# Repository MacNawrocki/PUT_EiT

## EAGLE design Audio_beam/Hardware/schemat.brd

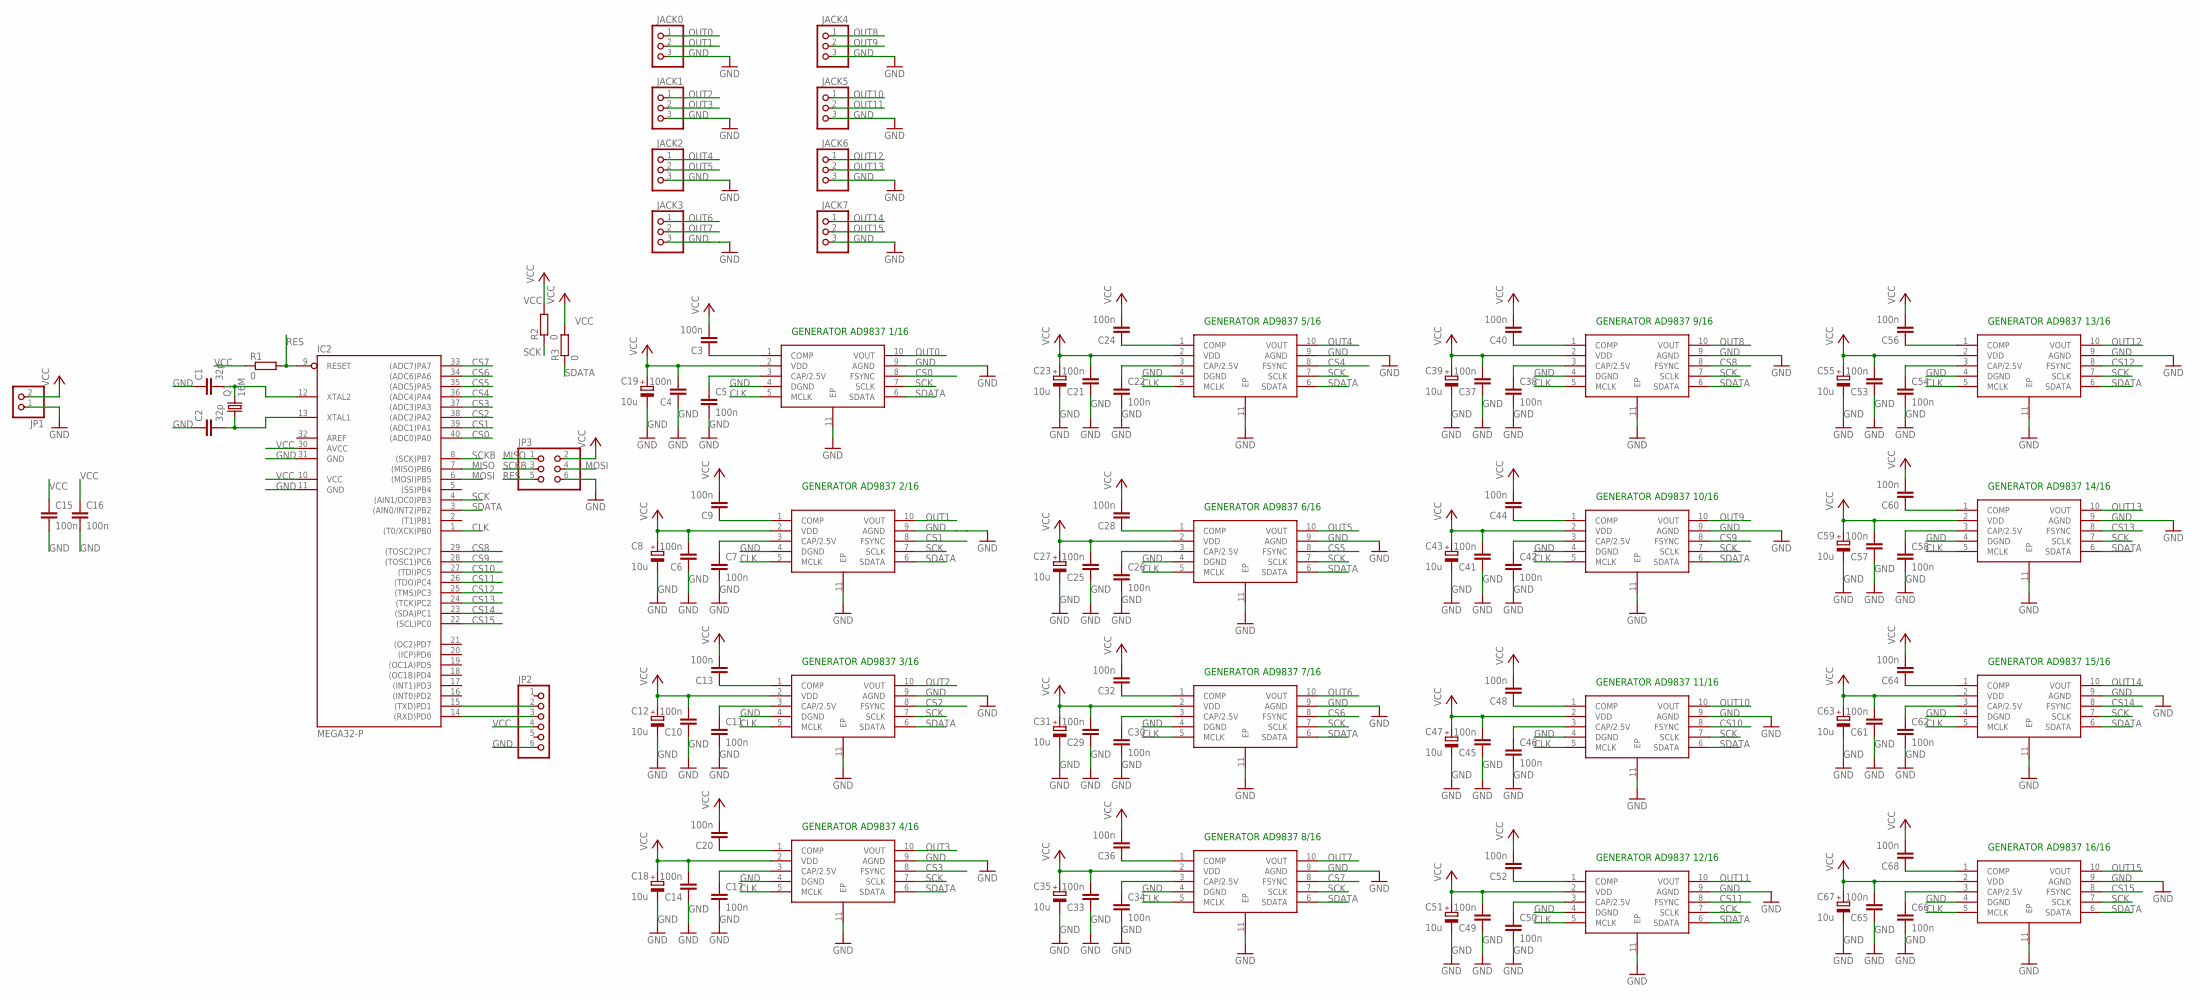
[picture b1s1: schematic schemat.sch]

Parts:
C1, C2: 32p; C1206
C3, C4, C5, C6, C7, C9, C10, C11, C13, C14, C15, C16, C17, C20, C21, C22, C24, C25, C26, C28, C29, C30, C32, C33, C34, C36, C37, C38, C40, C41, C42, C44, C45, C46, C48, C49, C50, C52, C53, C54, C56, C57, C58, C60, C61, C62, C64, C65, C66, C68: 100n; C1206
C8, C12, C18, C19, C23, C27, C31, C35, C39, C43, C47, C51, C55, C59, C63, C67: 10u; SMC_B
GEN1, GEN2, GEN3, GEN4, GEN5, GEN6, GEN7, GEN8, GEN9, GEN10, GEN11, GEN12, GEN13, GEN14, GEN15, GEN16: AD9837; SON50P300X300X80-11N
IC2: MEGA32-P; DIL40
JACK0, JACK1, JACK2, JACK3, JACK4, JACK5, JACK6, JACK7: PINHD-1X3; 1X03
JP1: PINHD-1X2; 1X02
JP2: PINHD-1X6; 1X06
JP3: PINHD-2X3; 2X03
Q1: 16M; HC49/S
R1: 0; R1206
R2, R3: 0; M1206

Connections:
CLK: GEN1.5 (MCLK), GEN2.5 (MCLK), GEN3.5 (MCLK), GEN4.5 (MCLK), GEN5.5 (MCLK), GEN6.5 (MCLK), GEN7.5 (MCLK), GEN8.5 (MCLK), GEN9.5 (MCLK), GEN10.5 (MCLK), GEN11.5 (MCLK), GEN12.5 (MCLK), GEN13.5 (MCLK), GEN14.5 (MCLK), GEN15.5 (MCLK), GEN16.5 (MCLK), IC2.1 ((T0/XCK)PB0)
CS0: GEN1.8 (FSYNC), IC2.40 ((ADC0)PA0)
CS1: GEN2.8 (FSYNC), IC2.39 ((ADC1)PA1)
CS2: GEN3.8 (FSYNC), IC2.38 ((ADC2)PA2)
CS3: GEN4.8 (FSYNC), IC2.37 ((ADC3)PA3)
CS4: GEN5.8 (FSYNC), IC2.36 ((ADC4)PA4)
CS5: GEN6.8 (FSYNC), IC2.35 ((ADC5)PA5)
CS6: GEN7.8 (FSYNC), IC2.34 ((ADC6)PA6)
CS7: GEN8.8 (FSYNC), IC2.33 ((ADC7)PA7)
CS8: GEN9.8 (FSYNC), IC2.29 ((TOSC2)PC7)
CS9: GEN10.8 (FSYNC), IC2.28 ((TOSC1)PC6)
CS10: GEN11.8 (FSYNC), IC2.27 ((TDI)PC5)
CS11: GEN12.8 (FSYNC), IC2.26 ((TDO)PC4)
CS12: GEN13.8 (FSYNC), IC2.25 ((TMS)PC3)
CS13: GEN14.8 (FSYNC), IC2.24 ((TCK)PC2)
CS14: GEN15.8 (FSYNC), IC2.23 ((SDA)PC1)
CS15: GEN16.8 (FSYNC), IC2.22 ((SCL)PC0)
GND: C1.1, C2.1, C4.1, C5.2, C6.1, C7.2, C8.-, C10.1, C11.2, C12.-, C14.1, C15.2, C16.2, C17.2, C18.-, C19.-, C21.1, C22.2, C23.-, C25.1, C26.2, C27.-, C29.1, C30.2, C31.-, C33.1, C34.2, C35.-, C37.1, C38.2, C39.-, C41.1, C42.2, C43.-, C45.1, C46.2, C47.-, C49.1, C50.2, C51.-, C53.1, C54.2, C55.-, C57.1, C58.2, C59.-, C61.1, C62.2, C63.-, C65.1, C66.2, C67.-, GEN1.4 (DGND), GEN1.9 (AGND), GEN1.11 (EP), GEN2.4 (DGND), GEN2.9 (AGND), GEN2.11 (EP), GEN3.4 (DGND), GEN3.9 (AGND), GEN3.11 (EP), GEN4.4 (DGND), GEN4.9 (AGND), GEN4.11 (EP), GEN5.4 (DGND), GEN5.9 (AGND), GEN5.11 (EP), GEN6.4 (DGND), GEN6.9 (AGND), GEN6.11 (EP), GEN7.4 (DGND), GEN7.9 (AGND), GEN7.11 (EP), GEN8.4 (DGND), GEN8.9 (AGND), GEN8.11 (EP), GEN9.4 (DGND), GEN9.9 (AGND), GEN9.11 (EP), GEN10.4 (DGND), GEN10.9 (AGND), GEN10.11 (EP), GEN11.4 (DGND), GEN11.9 (AGND), GEN11.11 (EP), GEN12.4 (DGND), GEN12.9 (AGND), GEN12.11 (EP), GEN13.4 (DGND), GEN13.9 (AGND), GEN13.11 (EP), GEN14.4 (DGND), GEN14.9 (AGND), GEN14.11 (EP), GEN15.4 (DGND), GEN15.9 (AGND), GEN15.11 (EP), GEN16.4 (DGND), GEN16.9 (AGND), GEN16.11 (EP), IC2.11 (GND), IC2.31 (GND), JACK0.3, JACK1.3, JACK2.3, JACK3.3, JACK4.3, JACK5.3, JACK6.3, JACK7.3, JP1.1, JP2.6, JP3.6
MISO: IC2.7 ((MISO)PB6), JP3.1
MOSI: IC2.6 ((MOSI)PB5), JP3.4
unnamed: C7.1, GEN2.3 (CAP/2.5V)
unnamed: C9.1, GEN2.1 (COMP)
unnamed: C1.2, IC2.12 (XTAL2), Q1.2
unnamed: C2.2, IC2.13 (XTAL1), Q1.1
unnamed: C5.1, GEN1.3 (CAP/2.5V)
unnamed: C11.1, GEN3.3 (CAP/2.5V)
unnamed: C13.1, GEN3.1 (COMP)
unnamed: C17.1, GEN4.3 (CAP/2.5V)
unnamed: C20.1, GEN4.1 (COMP)
unnamed: C22.1, GEN5.3 (CAP/2.5V)
unnamed: C24.1, GEN5.1 (COMP)
unnamed: C3.1, GEN1.1 (COMP)
unnamed: C26.1, GEN6.3 (CAP/2.5V)
unnamed: C28.1, GEN6.1 (COMP)
unnamed: C30.1, GEN7.3 (CAP/2.5V)
unnamed: C32.1, GEN7.1 (COMP)
unnamed: C34.1, GEN8.3 (CAP/2.5V)
unnamed: C36.1, GEN8.1 (COMP)
unnamed: C38.1, GEN9.3 (CAP/2.5V)
unnamed: C40.1, GEN9.1 (COMP)
unnamed: C42.1, GEN10.3 (CAP/2.5V)
unnamed: C44.1, GEN10.1 (COMP)
unnamed: C46.1, GEN11.3 (CAP/2.5V)
unnamed: C48.1, GEN11.1 (COMP)
unnamed: C50.1, GEN12.3 (CAP/2.5V)
unnamed: C52.1, GEN12.1 (COMP)
unnamed: C54.1, GEN13.3 (CAP/2.5V)
unnamed: C56.1, GEN13.1 (COMP)
unnamed: C58.1, GEN14.3 (CAP/2.5V)
unnamed: C60.1, GEN14.1 (COMP)
unnamed: C62.1, GEN15.3 (CAP/2.5V)
unnamed: C64.1, GEN15.1 (COMP)
unnamed: C66.1, GEN16.3 (CAP/2.5V)
unnamed: C68.1, GEN16.1 (COMP)
unnamed: IC2.15 ((TXD)PD1), JP2.2
unnamed: IC2.14 ((RXD)PD0), JP2.3
OUT0: GEN1.10 (VOUT), JACK0.1
OUT1: GEN2.10 (VOUT), JACK0.2
OUT2: GEN3.10 (VOUT), JACK1.1
OUT3: GEN4.10 (VOUT), JACK1.2
OUT4: GEN5.10 (VOUT), JACK2.1
OUT5: GEN6.10 (VOUT), JACK2.2
OUT6: GEN7.10 (VOUT), JACK3.1
OUT7: GEN8.10 (VOUT), JACK3.2
OUT8: GEN9.10 (VOUT), JACK4.1
OUT9: GEN10.10 (VOUT), JACK4.2
OUT10: GEN11.10 (VOUT), JACK5.1
OUT11: GEN12.10 (VOUT), JACK5.2
OUT12: GEN13.10 (VOUT), JACK6.1
OUT13: GEN14.10 (VOUT), JACK6.2
OUT14: GEN15.10 (VOUT), JACK7.1
OUT15: GEN16.10 (VOUT), JACK7.2
RES: IC2.9 (RESET), JP3.5, R1.2
SCK: GEN1.7 (SCLK), GEN2.7 (SCLK), GEN3.7 (SCLK), GEN4.7 (SCLK), GEN5.7 (SCLK), GEN6.7 (SCLK), GEN7.7 (SCLK), GEN8.7 (SCLK), GEN9.7 (SCLK), GEN10.7 (SCLK), GEN11.7 (SCLK), GEN12.7 (SCLK), GEN13.7 (SCLK), GEN14.7 (SCLK), GEN15.7 (SCLK), GEN16.7 (SCLK), IC2.4 ((AIN1/OC0)PB3), R2.1
SCKB: IC2.8 ((SCK)PB7), JP3.3
SDATA: GEN1.6 (SDATA), GEN2.6 (SDATA), GEN3.6 (SDATA), GEN4.6 (SDATA), GEN5.6 (SDATA), GEN6.6 (SDATA), GEN7.6 (SDATA), GEN8.6 (SDATA), GEN9.6 (SDATA), GEN10.6 (SDATA), GEN11.6 (SDATA), GEN12.6 (SDATA), GEN13.6 (SDATA), GEN14.6 (SDATA), GEN15.6 (SDATA), GEN16.6 (SDATA), IC2.3 ((AIN0/INT2)PB2), R3.1
VCC: C3.2, C4.2, C6.2, C8.+, C9.2, C10.2, C12.+, C13.2, C14.2, C15.1, C16.1, C18.+, C19.+, C20.2, C21.2, C23.+, C24.2, C25.2, C27.+, C28.2, C29.2, C31.+, C32.2, C33.2, C35.+, C36.2, C37.2, C39.+, C40.2, C41.2, C43.+, C44.2, C45.2, C47.+, C48.2, C49.2, C51.+, C52.2, C53.2, C55.+, C56.2, C57.2, C59.+, C60.2, C61.2, C63.+, C64.2, C65.2, C67.+, C68.2, GEN1.2 (VDD), GEN2.2 (VDD), GEN3.2 (VDD), GEN4.2 (VDD), GEN5.2 (VDD), GEN6.2 (VDD), GEN7.2 (VDD), GEN8.2 (VDD), GEN9.2 (VDD), GEN10.2 (VDD), GEN11.2 (VDD), GEN12.2 (VDD), GEN13.2 (VDD), GEN14.2 (VDD), GEN15.2 (VDD), GEN16.2 (VDD), IC2.10 (VCC), IC2.30 (AVCC), JP1.2, JP2.4, JP3.2, R1.1, R2.2, R3.2

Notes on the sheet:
GENERATOR AD9837 1/16
GENERATOR AD9837 2/16
GENERATOR AD9837 3/16
GENERATOR AD9837 4/16
GENERATOR AD9837 5/16
GENERATOR AD9837 6/16
GENERATOR AD9837 7/16
GENERATOR AD9837 8/16
GENERATOR AD9837 9/16
GENERATOR AD9837 10/16
GENERATOR AD9837 11/16
GENERATOR AD9837 12/16
GENERATOR AD9837 13/16
GENERATOR AD9837 14/16
GENERATOR AD9837 15/16
GENERATOR AD9837 16/16

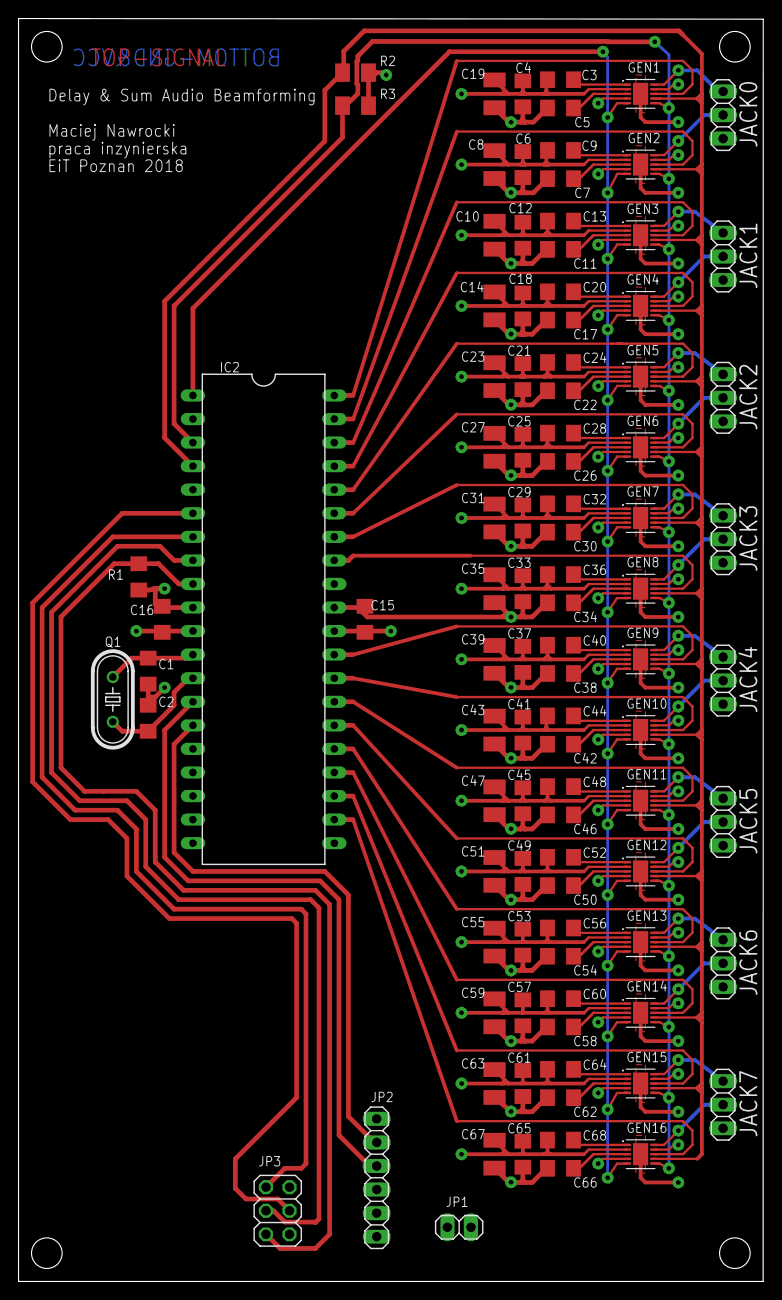
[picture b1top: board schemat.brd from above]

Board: 2 copper layers, 80.3 x 136.1 mm, 100 parts (0 on the bottom side), 77 nets.

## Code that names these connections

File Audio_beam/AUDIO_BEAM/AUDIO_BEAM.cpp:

//#ifndef F_CPU
//#define F_CPU 16000000UL
//#endif

#include <avr/io.h>
#include <math.h>
//#include <util/delay.h> 

//Chip Select 0
#define CSEL0 PA0
#define CSEL0_DDR	DDRA
#define CSEL0_PORT PORTA
//Chip Select 1
#define CSEL1 PA1
#define CSEL1_DDR	DDRA
#define CSEL1_PORT PORTA
//Chip Select 2
#define CSEL2 PA2
#define CSEL2_DDR	DDRA
#define CSEL2_PORT PORTA
//Chip Select 3
#define CSEL3 PA3
#define CSEL3_DDR	DDRA
#define CSEL3_PORT PORTA
//Chip Select 4
#define CSEL4 PA4
#define CSEL4_DDR	DDRA
#define CSEL4_PORT PORTA
//Chip Select 5
#define CSEL5 PA5
#define CSEL5_DDR	DDRA
#define CSEL5_PORT PORTA
//Chip Select 6
#define CSEL6 PA6
#define CSEL6_DDR	DDRA
#define CSEL6_PORT PORTA
//Chip Select 7
#define CSEL7 PA7
#define CSEL7_DDR	DDRA
#define CSEL7_PORT PORTA
//Chip Select 8
#define CSEL8 PC7
#define CSEL8_DDR	DDRC
#define CSEL8_PORT PORTC
//Chip Select 9
#define CSEL9 PC6
#define CSEL9_DDR	DDRC
#define CSEL9_PORT PORTC
//Chip Select 10
#define CSEL10 PC5
#define CSEL10_DDR	DDRC
#define CSEL10_PORT PORTC
//Chip Select 11
#define CSEL11 PC4
#define CSEL11_DDR	DDRC
#define CSEL11_PORT PORTC
//Chip Select 12
#define CSEL12 PC3
#define CSEL12_DDR	DDRC
#define CSEL12_PORT PORTC
//Chip Select 13
#define CSEL13 PC2
#define CSEL13_DDR	DDRC
#define CSEL13_PORT PORTC
//Chip Select 14
#define CSEL14 PC1
#define CSEL14_DDR	DDRC
#define CSEL14_PORT PORTC
//Chip Select 15
#define CSEL15 PC0
#define CSEL15_DDR	DDRC
#define CSEL15_PORT PORTC
//SCK do Software SPI
#define SCK PB3
#define SCK_DDR	DDRB
#define SCK_PORT PORTB
//SDATA do Software SPI
#define SDATA PB2
#define SDATA_DDR DDRB
#define SDATA_PORT PORTB
//CLK jako Fmclk czyli sygnał zegarowy referencyjny
#define CLK PB0
#define CLK_DDR DDRB
#define CLK_PORT PORTB

//Funkcje Software SPI 
//#define SET_INPUT(pin)			((pin ## _DDR) &= !_BV(pin) )
//#define SET_OUTPUT(ddr, pin)		(ddr |= (1<<pin))
#define SET_HIGH(pin)				((pin ## _PORT) |= _BV(pin))
#define SET_LOW(pin)				((pin ## _PORT) &= !_BV(pin))

#define TABSIZE 16
uint32_t phaseArray[TABSIZE];
//Czestotliwość fmclk - do przeliczania czestotliwosci oraz podawana na linii CLK
const float freqRef = 158000; 
uint16_t CalcPhase (uint32_t phase);
uint32_t CalcFreq(uint32_t freq);
void SPIconfig();
void SPIrefresh();
inline void SPIsend(uint16_t data); 
inline void SetAllCS_Low();
inline void SetAllCS_High();
void CalcPhaseVal(uint32_t freq, uint32_t dist);

//funkcja oblicza opóźnienia fazowe dla każdego generatora
void CalcPhaseVal(uint32_t freq, uint32_t dist)
{
	uint32_t spacing = 0.0725;//m    
    uint32_t speedSound = 343.0;// m/s
    uint32_t distxTab[TABSIZE];
    uint32_t maxdistx = spacing*7;
    for (int i = 0; i<TABSIZE; i++){
        if (i<7)distxTab[i]=(maxdistx-i*spacing)+spacing/2;
        if (i == 7)distxTab[i]=spacing/2;
        if (i == 8)distxTab[i]=spacing/2;
        if (i>8) distxTab[i]=spacing/2 + (i-8)*spacing;
    }
    uint32_t distRealTab[TABSIZE];
    for (int i = 0; i<TABSIZE; i++){
        distRealTab[i]=sqrt(pow(distxTab[i],2)+pow(dist,2));
    }
    uint32_t delayTab[TABSIZE];
    uint32_t delayzero=distRealTab[7]*speedSound;
    for (int i = 0; i<TABSIZE; i++){
        delayTab[i]=(distRealTab[i]*speedSound)-delayzero;
        phaseArray[i] = (1 - ((delayTab[i]/(1/freq))-floor((delayTab[i]/(1/freq)))))*2*3.14159265358979;
    }
}

//funkcja przelicza częstotliwość w Hz na dane do generatora
uint32_t CalcFreq(uint32_t freq)
{
	//f = fMCLK/2^28 × FREQREG
	float freqRes = 0x10000000;
	float stepSize;
	stepSize = freqRes/freqRef;
	
	uint32_t freqWord;
	freqWord = stepSize*freq;
	return freqWord;
}

//funkcja przelicza fazę na dane do generatora, faza podana w radianach
uint16_t CalcPhase (uint32_t phase)
{
	//2π/4096 × PHASEREG
	float phaseRes; 
	phaseRes = 4096/(2*3.14159265358979);
	uint16_t phaseWord;
	phaseWord = phase*phaseRes;
	return phaseWord;
}

//Konfiguracja pinów i ich rejestrów do SPI
void SPIconfig() 
{
	SCK_DDR|=1<<3; // SET_OUTPUT(SCK_DDR, SCK);
	SDATA_DDR|=1<<2; // SET_OUTPUT(SDATA_DDR,SDATA);
	//Rejestr DDR portu A zapełniony 1 - piny CSel0-7
	DDRA = 0b11111111;
	//Rejestr DDR portu C zapełniony 1 - piny CSel8-15
	DDRC = 0b11111111;
	SET_HIGH(SCK);
	SET_HIGH(SDATA);
	//Stan wysoki wszystkich FSYNC 
	PORTA = 0b11111111;
	PORTC = 0b11111111;
}

//Ustanowienie domyślnych wartości na portach SPI
void SPIrefresh()
{
	//Stan wysoki wszystkich FSYNC 
	PORTA = 0b11111111;
	PORTC = 0b11111111;
	SET_LOW(SDATA);
	SET_HIGH(SCK);
}

//Stan niski wszystkich FSYNC - dane odbierają wszystkie generatory
inline void SetAllCS_Low()
{
	PORTA = 0b00000000;
	PORTC = 0b00000000;
}

//Stan wysoki wszystkich FSYNC 
inline void SetAllCS_High()
{
	PORTA = 0b11111111;
	PORTC = 0b11111111;
}

//Funkcja software'owo realizuje komunikacje SPI - wysyła jeden wyraz
inline void SPIsend(uint16_t data) 
{
	for(uint16_t mask= 0x8000; mask; mask>>=1) 
	{
		SET_HIGH(SCK);
		if(data & mask) SET_HIGH(SDATA);
		else SET_LOW(SDATA);
		SET_LOW(SCK);
	}
}



int main(void)
{ 
	uint32_t freq = 5000; // częstotliwość generowanych sygnałów w Hz
	uint32_t dist = 2; // odległość punktu wzmocnienia sygnału od środka wektora głośników w m
	
	//kalkulowanie częstotliwości
	uint32_t freqWord = CalcFreq(freq);
	//wielkosc przesylanych danych do rejestru częstotliwości to 2 x 14 bit
	uint16_t freqWordMSB;
	uint16_t freqWordLSB;
	freqWordMSB = (int)((freqWord & 0xFFFC000)>>14);
	freqWordLSB = (int)(freqWord & 0x3FFF);
	//bity D15 i D14 - 01 wybierają rejestr FREQ0
	//freqWordLSB |= 0x4000;
	//freqWordMSB |= 0x4000; 
	freqWordLSB |= 0x4FFF;
	freqWordMSB |= 0x4FFF;
	
	//kalkulowanie fazy
	//wielkość przesyłanych danych do rejestru fazy to 12 bit 
	CalcPhaseVal(freq, dist);
	uint16_t phaseWordArray[TABSIZE];
	for (int i = 0; i<TABSIZE; i++){
        phaseWordArray[i]=CalcPhase(phaseArray[i]);
		//bity D15, D14, D13- 110 wybierają rejestr PHASE0
		phaseWordArray[i]|= 0xC000;
    }
	
	uint16_t initWord = 0x2100;	// bity D13 i D8 - zapis danych i RESET=1
	// RESET=0, bity D11 i  D10 = 00 - rejsestry FREQ0 i PHASE0
	uint16_t resetWordSin = 0x2000; // wyjście to sin
	uint16_t resetWordSqr = 0x2020; // wyjście to prostokąt
	uint16_t resetWordTri = 0x2002; // wyjście to trójkąt
	
	SPIconfig();
	
	//Podanie do wszystkich generatorów informacji o częstotliwości i RESET = 1
	//SetAllCS_Low();
	SET_LOW(CSEL0);	
	SPIsend(initWord); 
	SET_HIGH(CSEL0);
	//SetAllCS_High();
	SPIrefresh();
	SetAllCS_Low();	
	SPIsend(freqWordLSB);
	SetAllCS_High();
	SPIrefresh();
	SetAllCS_Low();	
	SPIsend(freqWordMSB);
	SetAllCS_High();
	SPIrefresh();
	
	/*
	//podanie do Generatora 0 informacji o fazie
	SET_LOW(CSEL0);
	SPIsend(phaseWordArray[0]);
	SET_HIGH(CSEL0);
	SPIrefresh();
	//podanie do Generatora 1 informacji o fazie
	SET_LOW(CSEL1);
	SPIsend(phaseWordArray[1]);
	SET_HIGH(CSEL1);
	SPIrefresh();
	//podanie do Generatora 2 informacji o fazie
	SET_LOW(CSEL2);
	SPIsend(phaseWordArray[2]);
	SET_HIGH(CSEL2);
	SPIrefresh();
	//podanie do Generatora 3 informacji o fazie
	SET_LOW(CSEL3);
	SPIsend(phaseWordArray[3]);
	SET_HIGH(CSEL3);
	SPIrefresh();
	//podanie do Generatora 4 informacji o fazie
	SET_LOW(CSEL4);
	SPIsend(phaseWordArray[4]);
	SET_HIGH(CSEL4);
	SPIrefresh();
	//podanie do Generatora 5 informacji o fazie
	SET_LOW(CSEL5);
	SPIsend(phaseWordArray[5]);
	SET_HIGH(CSEL5);
	SPIrefresh();
	//podanie do Generatora 6 informacji o fazie
	SET_LOW(CSEL6);
	SPIsend(phaseWordArray[6]);
	SET_HIGH(CSEL6);
	SPIrefresh();
	//podanie do Generatora 7 informacji o fazie
	SET_LOW(CSEL7);
	SPIsend(phaseWordArray[7]);
	SET_HIGH(CSEL7);
	SPIrefresh();
	//podanie do Generatora 8 informacji o fazie
	SET_LOW(CSEL8);
	SPIsend(phaseWordArray[8]);
	SET_HIGH(CSEL8);
	SPIrefresh();
	//podanie do Generatora 9 informacji o fazie
	SET_LOW(CSEL9);
	SPIsend(phaseWordArray[9]);
	SET_HIGH(CSEL9);
	SPIrefresh();
	//podanie do Generatora 10 informacji o fazie
	SET_LOW(CSEL10);
	SPIsend(phaseWordArray[10]);
	SET_HIGH(CSEL10);
	SPIrefresh();
	//podanie do Generatora 11 informacji o fazie
	SET_LOW(CSEL11);
	SPIsend(phaseWordArray[11]);
	SET_HIGH(CSEL11);
	SPIrefresh();
	//podanie do Generatora 12 informacji o fazie
	SET_LOW(CSEL12);
	SPIsend(phaseWordArray[12]);
	SET_HIGH(CSEL12);
	SPIrefresh();
	//podanie do Generatora 13 informacji o fazie
	SET_LOW(CSEL13);
	SPIsend(phaseWordArray[13]);
	SET_HIGH(CSEL13);
	//podanie do Generatora 14 informacji o fazie
	SET_LOW(CSEL14);
	SPIsend(phaseWordArray[14]);
	SET_HIGH(CSEL14);
	SPIrefresh();
	//podanie do Generatora 15 informacji o fazie
	SET_LOW(CSEL15);
	SPIsend(phaseWordArray[15]);
	SET_HIGH(CSEL15);	*/
	SPIrefresh();

	//Podanie do wszystkich generatorów informacji o trybie pracy i RESET = 0
	SetAllCS_Low();
	SPIsend(resetWordSin); 
	SetAllCS_High();
	
	//Po podaniu danych do generatorów uruchamiany jest generator CLK
	//CLK generowane tą metodą ma częstotliwość 158 kHz
	CLK_DDR|=1; // SET_OUTPUT(CLK_DDR, CLK);
	while(1)
    {
		SET_HIGH(CLK);
		SET_LOW(CLK);	
	}
	
}

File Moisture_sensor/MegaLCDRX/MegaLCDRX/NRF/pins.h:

#ifndef PINS_H_
#define PINS_H_

/*
Connection:
ATMega328PB	PIN	To
PB3	to	MOSI		programator/radio
PB4	to	MISO		programator/radio
PB5	to	SCK			programator/radio
PB6	to	CSN			radio
PB7	to	CE			radio
PC0	to	LCD_RST		wywietlacz
PC1	to	LCD_AO		wywietlacz
PC2	to	LCD_MOSI	wywietlacz
PC3	to	LCD_SCK		wywietlacz
PC4	to	LED			dioda na p³ytce
PC6	to	RESET		programator/radio
PD0	to	RX
PD1	to	TX
PD2	to	BUTTON1		guzik na p³ytce
PE3	to	LCD_CS		wywietlacz
*/ 

#define BIT(x)				1<<(x)
#define SET_BIT(x, y)		(x) |= (BIT(y))
#define CLEAR_BIT(x, y)		(x) &= (~(BIT(y)))
#define SET_OUTPUT(pin)		(pin ## _DDR)|=_BV(pin)
#define SET_INPUT(pin)		CLEAR_BIT((pin ## _DDR),(pin))
#define SET_HIGH(pin)		(pin ## _PORT)|=_BV(pin)
#define SET_LOW(pin)		(pin ## _PORT)&=!_BV(pin)

#define MOSI PB3
#define MOSI_DDR DDRB
#define MOSI_PORT PORTB

#define MISO PB4
#define MISO_DDR DDRB
#define MISO_PORT PORTB
#define MISO_PIN  PINB


#define SCK PB5
#define SCK_DDR DDRB
#define SCK_PORT PORTB

#define CSN PB6
#define CSN_DDR DDRB
#define CSN_PORT PORTB

#define CE PB7
#define CE_DDR DDRB
#define CE_PORT PORTB

#define LCD_RST PC0
#define LCD_RST_DDR DDRC
#define LCD_RST_PORT PORTC

#define LCD_AO PC1
#define LCD_AO_DDR DDRC
#define LCD_AO_PORT PORTC

#define LCD_MOSI PC2
#define LCD_MOSI_DDR DDRC
#define LCD_MOSI_PORT PORTC

#define LCD_SCK PC3
#define LCD_SCK_DDR DDRC
#define LCD_SCK_PORT PORTC

#define LED PC4
#define LED_DDR DDRC
#define LED_PORT PORTC

#define BUTTON PD2
#define BUTTON_DDR DDRD
#define BUTTON_PORT PORTD

#define LCD_CSS PE3
#define LCD_CSS_DDR DDRE
#define LCD_CSS_PORT PORTE

#endif /* PINS_H_ */
